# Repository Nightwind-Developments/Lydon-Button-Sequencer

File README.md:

# Lydon-Button-Sequencer
PCB Design resources made by Nightwind Developments for PeoplePerHour client, Lydon P.

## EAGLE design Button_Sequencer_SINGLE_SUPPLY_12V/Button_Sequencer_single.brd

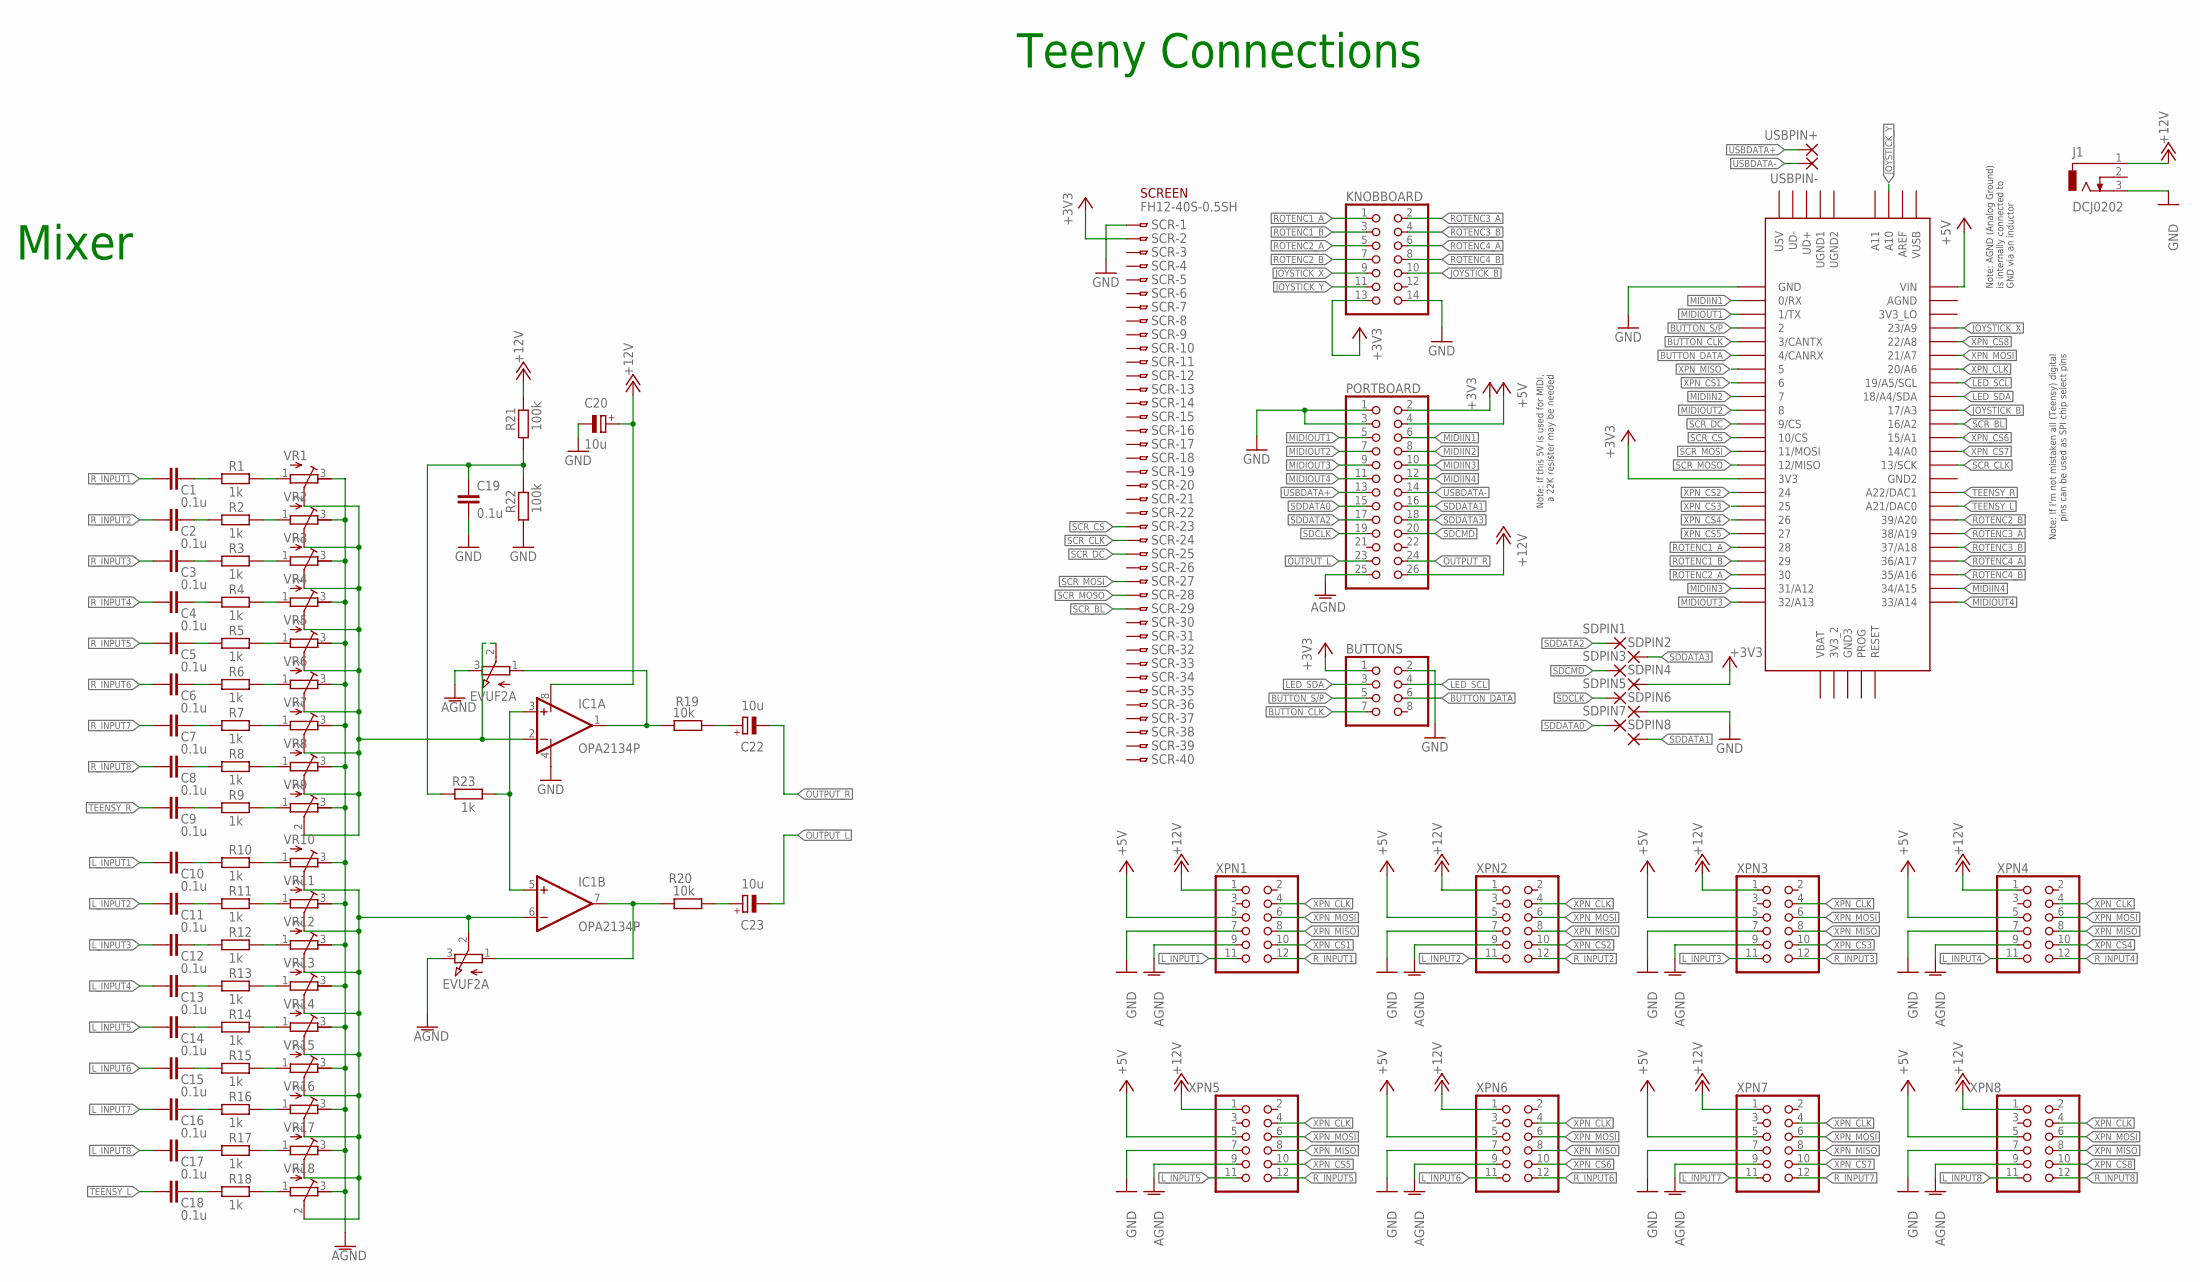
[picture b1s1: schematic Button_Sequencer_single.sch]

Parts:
BUTTONS: PINHD-2X4; 2X04
C1, C2, C3, C4, C5, C6, C7, C8, C9, C10, C11, C12, C13, C14, C15, C16, C17, C18: 0.1u; C025-030X050
C19: 0.1u; C0805
C20, C22, C23: 10u; E5-10,5
IC1: OPA2134P; DIL08
J1: DCJ0202
KNOBBOARD: PINHD-2X7; 2X07
PORTBOARD: PINHD-2X13; 2X13
R1, R2, R3, R4, R5, R6, R7, R8, R9, R10, R11, R12, R13, R14, R15, R16, R17, R18, R23: 1k; R0805
R19, R20: 10k; R0805
R21, R22: 100k; R0805
SCR: FH12-40S-0.5SH
SDPIN1, SDPIN2, SDPIN3, SDPIN4, SDPIN5, SDPIN6, SDPIN7, SDPIN8: 1,6/0,8
TEENSY_3.6: TEENSY_3.5/3.6
USBPIN+: 1,6/0,8
USBPIN-: 1,6/0,8
VR1, VR2, VR3, VR4, VR5, VR6, VR7, VR8, VR9, VR10, VR11, VR12, VR13, VR14, VR15, VR16, VR17, VR18: R-TRIMM3339P; RTRIM3339P
VR19, VR20: EVUF2A; EVUF
XPN1, XPN2, XPN3, XPN4, XPN5, XPN6, XPN7, XPN8: PINHD-2X6; 2X06

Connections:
+3V3: BUTTONS.1, KNOBBOARD.13, PORTBOARD.2, SCR.2, SDPIN4.1, TEENSY_3.6.3V3
+5V: PORTBOARD.4, TEENSY_3.6.VIN, XPN1.5, XPN2.5, XPN3.5, XPN4.5, XPN5.5, XPN6.5, XPN7.5, XPN8.5
+12V: C20.+, IC1.8 (V+), J1.1, PORTBOARD.26, R21.2, XPN1.1, XPN2.1, XPN3.1, XPN4.1, XPN5.1, XPN6.1, XPN7.1, XPN8.1
AGND: PORTBOARD.25, VR1.3 (E), VR2.3 (E), VR3.3 (E), VR4.3 (E), VR5.3 (E), VR6.3 (E), VR7.3 (E), VR8.3 (E), VR9.3 (E), VR10.3 (E), VR11.3 (E), VR12.3 (E), VR13.3 (E), VR14.3 (E), VR15.3 (E), VR16.3 (E), VR17.3 (E), VR18.3 (E), VR19.3 (E), VR20.3 (E), XPN1.9, XPN2.9, XPN3.9, XPN4.9, XPN5.9, XPN6.9, XPN7.9, XPN8.9
BUTTON_CLK: BUTTONS.7, TEENSY_3.6.3/CANTX
BUTTON_DATA: BUTTONS.6, TEENSY_3.6.4/CANRX
BUTTON_S/P: BUTTONS.5, TEENSY_3.6.2
GND: BUTTONS.2, C19.2, C20.-, IC1.4 (V-), J1.3, KNOBBOARD.14, PORTBOARD.1, PORTBOARD.3, R22.1, SCR.1, SDPIN6.1, TEENSY_3.6.GND, XPN1.7, XPN2.7, XPN3.7, XPN4.7, XPN5.7, XPN6.7, XPN7.7, XPN8.7
JOYSTICK_B: KNOBBOARD.10, TEENSY_3.6.17/A3
JOYSTICK_X: KNOBBOARD.9, TEENSY_3.6.23/A9
JOYSTICK_Y: KNOBBOARD.11, TEENSY_3.6.A10
LED_SCL: BUTTONS.4, TEENSY_3.6.19/A5/SCL
LED_SDA: BUTTONS.3, TEENSY_3.6.18/A4/SDA
LEFT_OP_OUT: IC1.7 (OUT), R20.2, VR20.1 (A)
L_INPUT1: C10.2, XPN1.11
L_INPUT2: C11.2, XPN2.11
L_INPUT3: C12.2, XPN3.11
L_INPUT4: C13.2, XPN4.11
L_INPUT5: C14.2, XPN5.11
L_INPUT6: C15.2, XPN6.11
L_INPUT7: C16.2, XPN7.11
L_INPUT8: C17.2, XPN8.11
L_OP_IN: IC1.6 (-IN), VR10.2 (S), VR11.2 (S), VR12.2 (S), VR13.2 (S), VR14.2 (S), VR15.2 (S), VR16.2 (S), VR17.2 (S), VR18.2 (S), VR20.2 (S)
MIDIIN1: PORTBOARD.6, TEENSY_3.6.0/RX
MIDIIN2: PORTBOARD.8, TEENSY_3.6.7
MIDIIN3: PORTBOARD.10, TEENSY_3.6.31/A12
MIDIIN4: PORTBOARD.12, TEENSY_3.6.34/A15
MIDIOUT1: PORTBOARD.5, TEENSY_3.6.1/TX
MIDIOUT2: PORTBOARD.7, TEENSY_3.6.8
MIDIOUT3: PORTBOARD.9, TEENSY_3.6.32/A13
MIDIOUT4: PORTBOARD.11, TEENSY_3.6.33/A14
unnamed: C4.1, R4.1
unnamed: C22.+, R19.1
unnamed: C1.1, R1.1
unnamed: C2.1, R2.1
unnamed: C3.1, R3.1
unnamed: C9.1, R9.1
unnamed: R9.2, VR9.1 (A)
unnamed: C10.1, R10.1
unnamed: R10.2, VR10.1 (A)
unnamed: R3.2, VR3.1 (A)
unnamed: C11.1, R11.1
unnamed: IC1.3 (+IN), IC1.5 (+IN), R23.1
unnamed: R1.2, VR1.1 (A)
unnamed: R4.2, VR4.1 (A)
unnamed: C12.1, R12.1
unnamed: C13.1, R13.1
unnamed: R13.2, VR13.1 (A)
unnamed: R2.2, VR2.1 (A)
unnamed: C19.1, R21.1, R22.2, R23.2
unnamed: C23.+, R20.1
unnamed: R11.2, VR11.1 (A)
unnamed: R12.2, VR12.1 (A)
unnamed: C5.1, R5.1
unnamed: C6.1, R6.1
unnamed: C7.1, R7.1
unnamed: R7.2, VR7.1 (A)
unnamed: R5.2, VR5.1 (A)
unnamed: R6.2, VR6.1 (A)
unnamed: C8.1, R8.1
unnamed: R8.2, VR8.1 (A)
unnamed: C14.1, R14.1
unnamed: R14.2, VR14.1 (A)
unnamed: C15.1, R15.1
unnamed: C16.1, R16.1
unnamed: C17.1, R17.1
unnamed: R17.2, VR17.1 (A)
unnamed: R15.2, VR15.1 (A)
unnamed: R16.2, VR16.1 (A)
unnamed: C18.1, R18.1
unnamed: R18.2, VR18.1 (A)
OUTPUT_L: C23.-, PORTBOARD.23
OUTPUT_R: C22.-, PORTBOARD.24
RIGHT_OP_OUT: IC1.1 (OUT), R19.2, VR19.1 (A)
ROTENC1_A: KNOBBOARD.1, TEENSY_3.6.28
ROTENC1_B: KNOBBOARD.3, TEENSY_3.6.29
ROTENC2_A: KNOBBOARD.5, TEENSY_3.6.30
ROTENC2_B: KNOBBOARD.7, TEENSY_3.6.39/A20
ROTENC3_A: KNOBBOARD.2, TEENSY_3.6.38/A19
ROTENC3_B: KNOBBOARD.4, TEENSY_3.6.37/A18
ROTENC4_A: KNOBBOARD.6, TEENSY_3.6.36/A17
ROTENC4_B: KNOBBOARD.8, TEENSY_3.6.35/A16
R_INPUT1: C1.2, XPN1.12
R_INPUT2: C2.2, XPN2.12
R_INPUT3: C3.2, XPN3.12
R_INPUT4: C4.2, XPN4.12
R_INPUT5: C5.2, XPN5.12
R_INPUT6: C6.2, XPN6.12
R_INPUT7: C7.2, XPN7.12
R_INPUT8: C8.2, XPN8.12
R_OP_IN: IC1.2 (-IN), VR1.2 (S), VR2.2 (S), VR3.2 (S), VR4.2 (S), VR5.2 (S), VR6.2 (S), VR7.2 (S), VR8.2 (S), VR9.2 (S), VR19.2 (S)
SCR_BL: SCR.29, TEENSY_3.6.16/A2
SCR_CLK: SCR.24, TEENSY_3.6.13/SCK
SCR_CS: SCR.23, TEENSY_3.6.10/CS
SCR_DC: SCR.25, TEENSY_3.6.9/CS
SCR_MOSI: SCR.27, TEENSY_3.6.11/MOSI
SCR_MOSO: SCR.28, TEENSY_3.6.12/MISO
SDCLK: PORTBOARD.19, SDPIN5.1
SDCMD: PORTBOARD.20, SDPIN3.1
SDDATA0: PORTBOARD.15, SDPIN7.1
SDDATA1: PORTBOARD.16, SDPIN8.1
SDDATA2: PORTBOARD.17, SDPIN1.1
SDDATA3: PORTBOARD.18, SDPIN2.1
TEENSY_L: C18.2, TEENSY_3.6.21/DAC0 (A21/DAC0)
TEENSY_R: C9.2, TEENSY_3.6.A22/DAC1
USBDATA+: PORTBOARD.13, USBPIN+.1
USBDATA-: PORTBOARD.14, USBPIN-.1
XPN_CLK: TEENSY_3.6.20/A6, XPN1.4, XPN2.4, XPN3.4, XPN4.4, XPN5.4, XPN6.4, XPN7.4, XPN8.4
XPN_CS1: TEENSY_3.6.6, XPN1.10
XPN_CS2: TEENSY_3.6.24, XPN2.10
XPN_CS3: TEENSY_3.6.25, XPN3.10
XPN_CS4: TEENSY_3.6.26, XPN4.10
XPN_CS5: TEENSY_3.6.27, XPN5.10
XPN_CS6: TEENSY_3.6.15/A1, XPN6.10
XPN_CS7: TEENSY_3.6.14/A0, XPN7.10
XPN_CS8: TEENSY_3.6.22/A8, XPN8.10
XPN_MISO: TEENSY_3.6.5, XPN1.8, XPN2.8, XPN3.8, XPN4.8, XPN5.8, XPN6.8, XPN7.8, XPN8.8
XPN_MOSI: TEENSY_3.6.21/A7, XPN1.6, XPN2.6, XPN3.6, XPN4.6, XPN5.6, XPN6.6, XPN7.6, XPN8.6

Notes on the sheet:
Teeny Connections
Mixer
SCREEN
Note: AGND (Analog Ground) is internally connected to GND via an inductor
Note: If this 5V is used for MIDI, a 22K resister may be needed
Note: If I'm not mistaken all (Teensy) digital pins can be used as SPI chip select pins

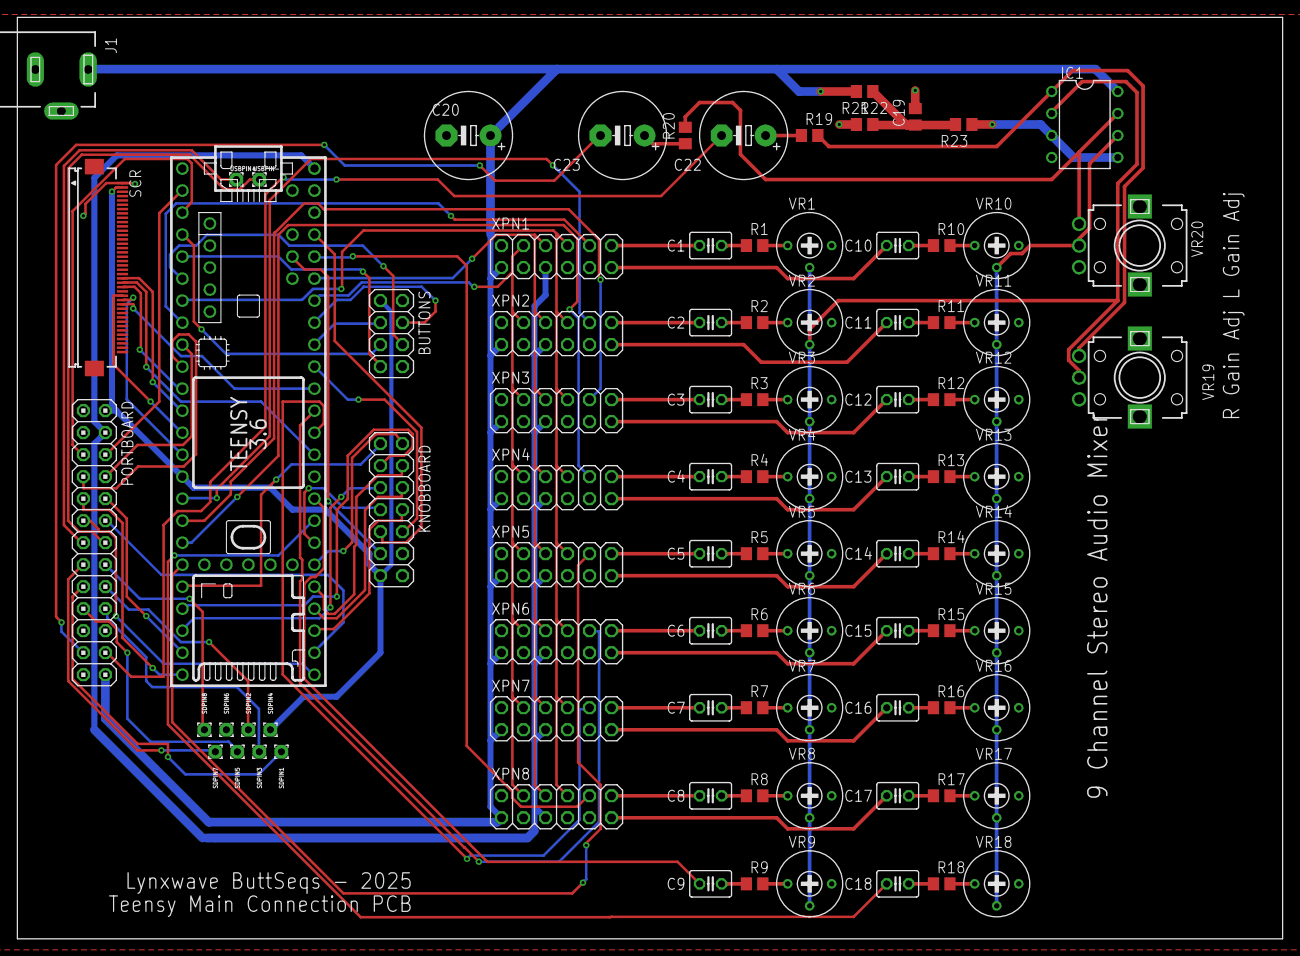
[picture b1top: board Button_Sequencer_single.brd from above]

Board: 2 copper layers, 146.0 x 106.3 mm, 90 parts (0 on the bottom side), 118 nets.

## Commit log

2020-03-22 Added lib dir and teensy eagle .lbr
2020-03-25 added the teensy library and created sch and brd
2020-03-30 Schematic and pcb files for buttons bouard
2020-03-30 Schematic and pcb files for knobs board
2020-03-30 Schematic and pcb files for ports board
2020-04-01 datasheets and pinout documentation
2020-04-03 main update and unused restructured
2020-04-03 milestone all connectors sch TODO routing and expansion
2020-04-04 pcb cleanup and audio_main tidy
2020-04-10 general expansion slots
2020-04-11 MIDI pinout connections, backup files cleanup, gitignore
2020-04-11 rm local backups
2020-04-11 button expansion
2020-04-11 Milestone fully drafted
2020-04-14 Lib dir remanagment
2020-04-14 KNOBBOARD pinout fixed, seperate audio ground added, pinhead lib switched to, pcb rerouted. TODO general expansion and mixing
2020-04-14 PDFs of sch & brd
2020-04-15 microSD adapter PCB gerber files
2020-04-15 xpn-SPI connected, portboard audio added
2020-04-15 milestone, reroute
2020-04-15 pdf export
2020-04-19 Added 8 channel audio xpn to general board (inc. pdf)
2020-04-19 Reorganised directory structure to add audio_mixer board
2020-04-19 Audio Mixer half done
2020-04-20 mixer schematic functionally done, todo labels and brd
2020-05-01 Main Board Complete!
2020-05-01 Lib change
2020-05-01 Mixer Design complete
2020-05-01 audio mixer comlpete!
2020-05-07 Create LICENSE
2020-06-06 old seperate files
2020-06-06 ammended schematic
2020-06-06 ammendments routing
2020-06-06 PCD, data unrouted
2020-06-06 fixed power
2020-06-09 Fixed lost commit from merger
2020-06-09 PDF exports
2020-06-16 Added +-12V barrel connetor TODO single +12V supply varient
2020-06-16 Removed -12V, single supply version w/ jack. COMPLETE
